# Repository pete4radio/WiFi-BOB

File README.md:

# WiFi-BOB
Breakout board for a WiFi or WiFi/LoRa module

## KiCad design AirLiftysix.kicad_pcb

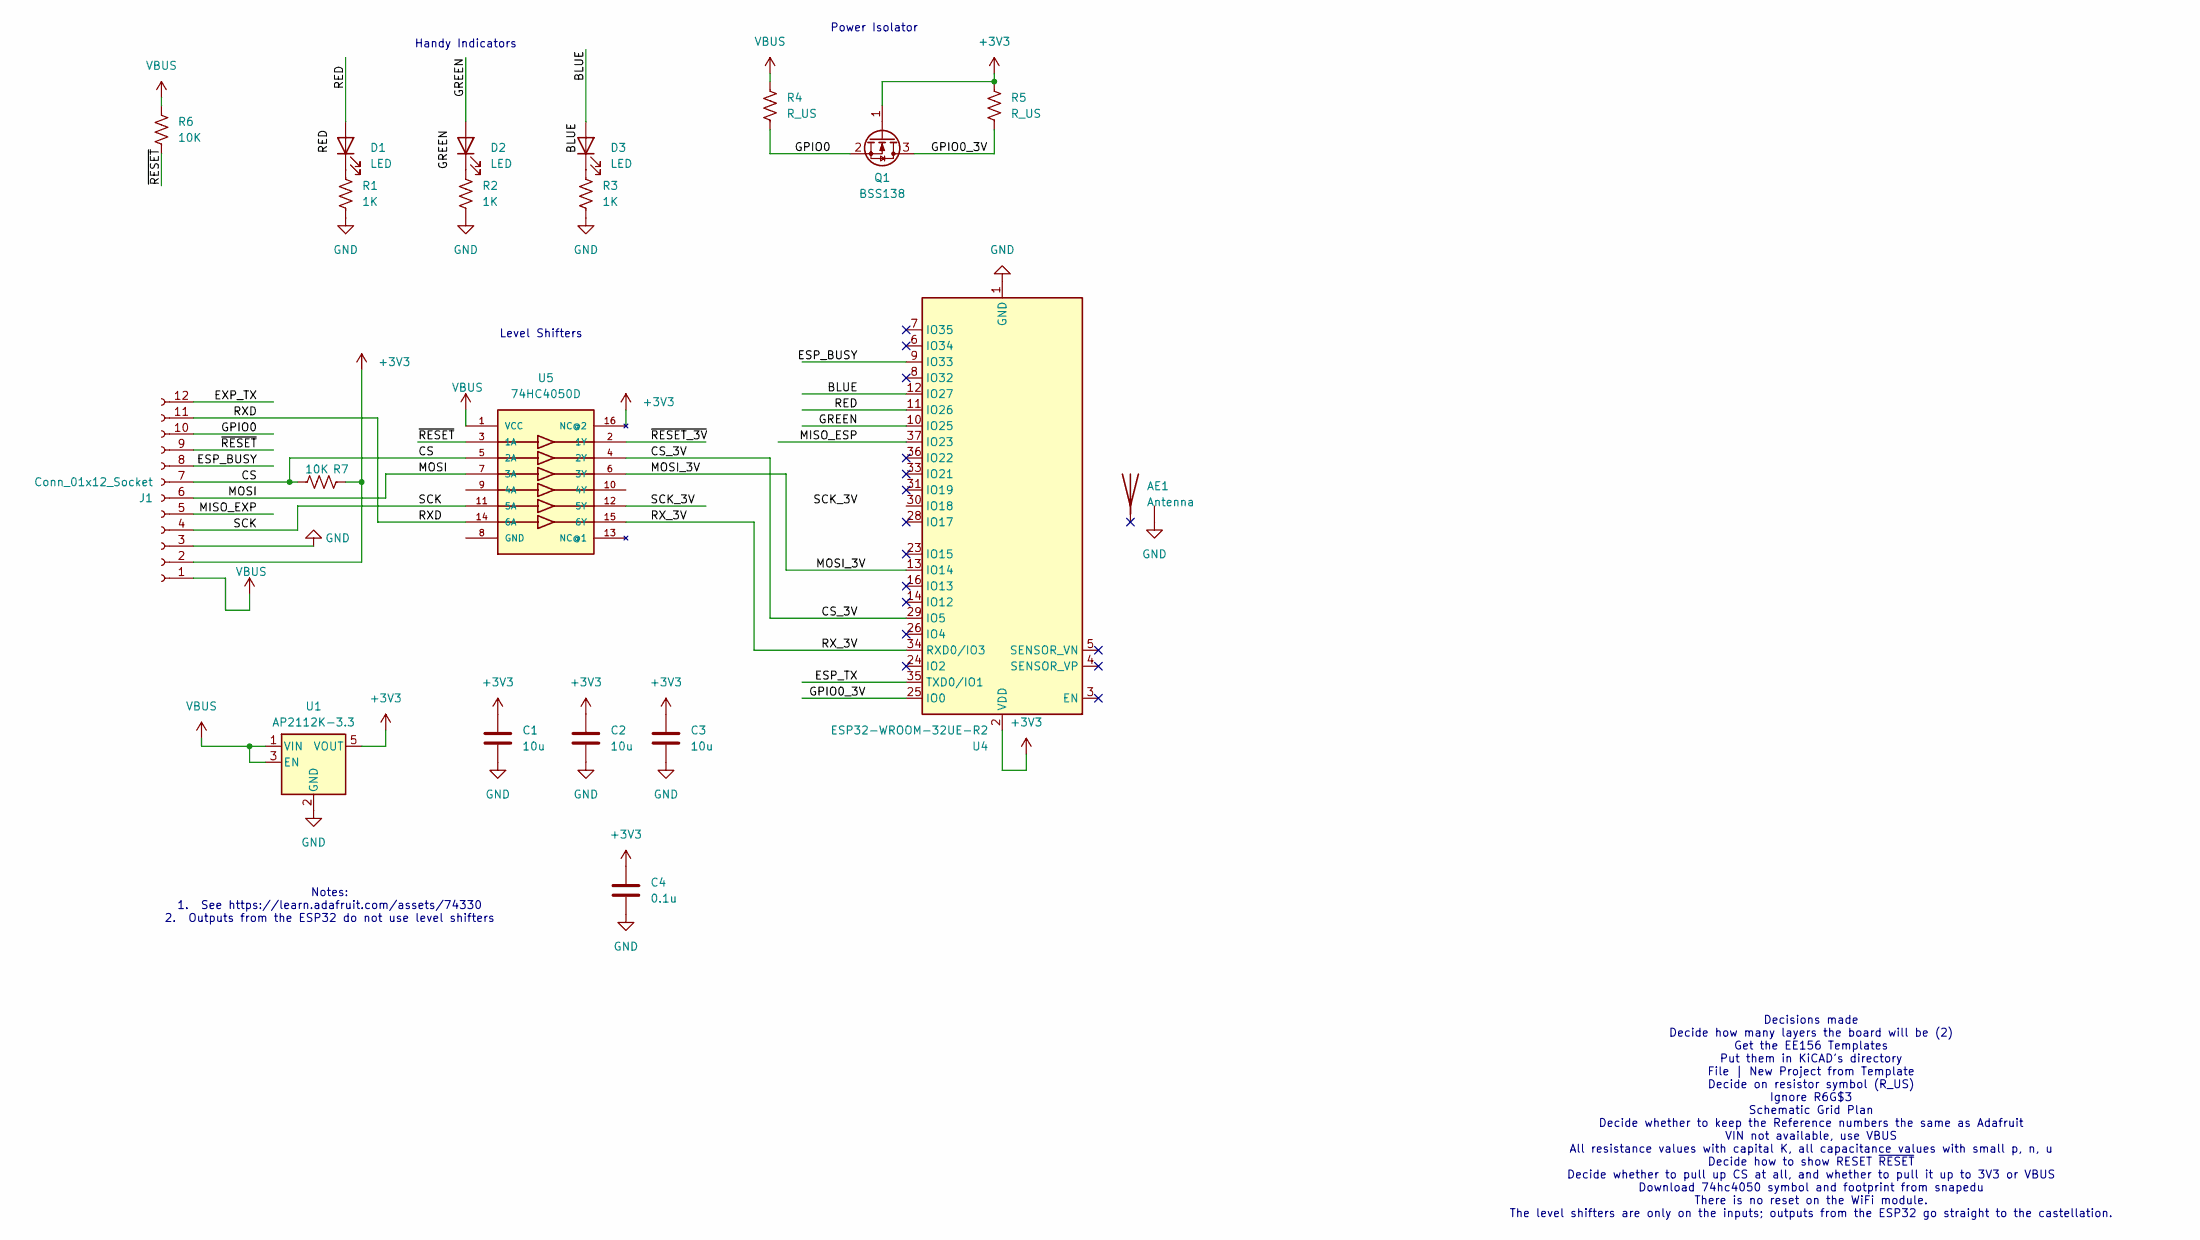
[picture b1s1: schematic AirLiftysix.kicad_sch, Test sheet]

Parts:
AE1: Antenna; Texas_SWRA117D_2.4GHz_Left
C1, C2, C3: 10u; C_0201_0603Metric_Pad0.64x0.40mm_HandSolder
C4: 0.1u; C_0201_0603Metric_Pad0.64x0.40mm_HandSolder
D1, D2, D3: LED; LED_0603_1608Metric_Pad1.05x0.95mm_HandSolder
J1: Conn_01x12_Socket; PinHeader_1x12_P2.54mm_Vertical
Q1: BSS138; SOT-23
R1, R2, R3: 1K; R_0201_0603Metric_Pad0.64x0.40mm_HandSolder
R4, R5: R_US; R_0201_0603Metric_Pad0.64x0.40mm_HandSolder
R6, R7: 10K; R_0201_0603Metric_Pad0.64x0.40mm_HandSolder
U1: AP2112K-3.3; SOT-23-5
U4: ESP32-WROOM-32UE-R2; ESP32-WROOM-32UE
U5: 74HC4050D; SOIC-16_3.9x9.9mm_P1.27mm; DigiKey_Part_Number 74HC4050DCT-ND

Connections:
+3V3: C1.1, C2.1, C3.1, C4.1, J1.2, Q1.1 (G), R5.1, R7.1, U1.5 (VOUT), U4.2 (VDD), U5.16 (NC@2)
/BLUE: D3.2 (A), U4.12 (IO27)
/CS: J1.7, R7.2, U5.5 (2A)
/CS_3V: U4.29 (IO5), U5.4 (2Y)
/ESP_BUSY: J1.8, U4.9 (IO33)
/ESP_TX: U4.35 (TXD0/IO1)
/EXP_TX: J1.12
/GPIO0: J1.10, Q1.2 (S), R4.2
/GPIO0_3V: Q1.3 (D), R5.2, U4.25 (IO0)
/GREEN: D2.2 (A), U4.10 (IO25)
/MISO_ESP: U4.37 (IO23)
/MISO_EXP: J1.5
/MOSI: J1.6, U5.7 (3A)
/MOSI_3V: U4.13 (IO14), U5.6 (3Y)
/RED: D1.2 (A), U4.11 (IO26)
/RXD: J1.11, U5.14 (6A)
/RX_3V: U4.34 (RXD0/IO3), U5.15 (6Y)
/SCK: J1.4, U5.11 (5A)
/SCK_3V: U5.12 (5Y)
/~RESET_3V: U5.2 (1Y)
/~RESET: J1.9, R6.2, U5.3 (1A)
GND: AE1.2 (ground), C1.2, C2.2, C3.2, C4.2, J1.3, R1.2, R2.2, R3.2, U1.2 (GND), U4.1 (GND), U4.15 (GND), U4.38 (GND), U4.39 (GND)
unnamed: D1.1 (K), R1.1
unnamed: D2.1 (K), R2.1
unnamed: D3.1 (K), R3.1
VBUS: J1.1, R4.1, R6.1, U1.1 (VIN), U1.3 (EN), U5.1 (VCC)

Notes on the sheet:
Handy Indicators
Notes: 1. See https://learn.adafruit.com/assets/74330 2. Outputs from the ESP32 do not use level shifters
Level Shifters
Decisions made Decide how many layers the board will be (2) Get the EE156 Templates Put them in KiCAD's directory File | New Project from Template Decide on resistor symbol (R_US) Ignore R6G$3 Schematic Grid Plan Decide whether to keep the Reference numbers the same as Adafruit VIN not available, u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
Power Isolator

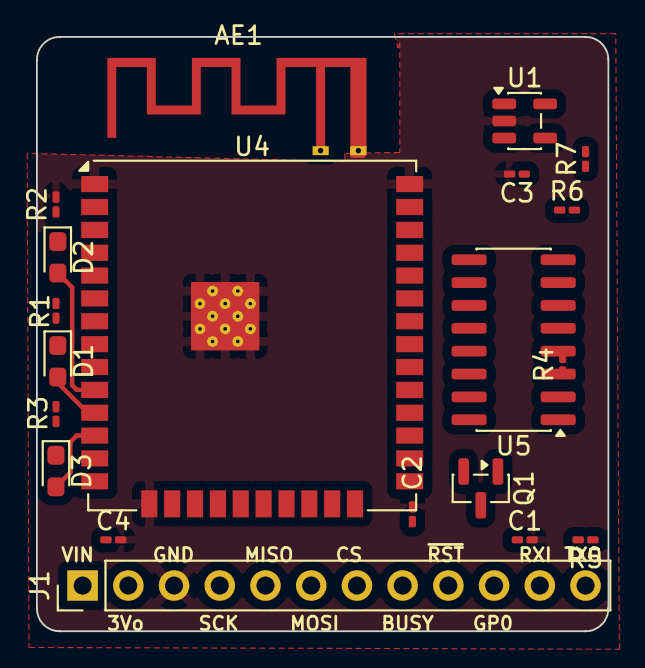
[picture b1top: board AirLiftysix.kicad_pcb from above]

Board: 2 copper layers, 31.8 x 33.0 mm, 20 parts (0 on the bottom side), 20 nets.

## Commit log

2026-01-21 initial commit; basics of schematic are in
2026-01-26 started on PCB
2026-01-26 includes antenna
2026-01-27 antenna, new floorplan
2026-01-27 Added notes to PCB
